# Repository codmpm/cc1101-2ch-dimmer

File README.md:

# CC1101 2ch PWM LED Dimmer

This is a prototype on an 2-channel PWM LED Dimmer which should work with the marvelous AskSin++ library.

Readme will be populated over time...

# License
codm.de, 2019, CC-BY-NC

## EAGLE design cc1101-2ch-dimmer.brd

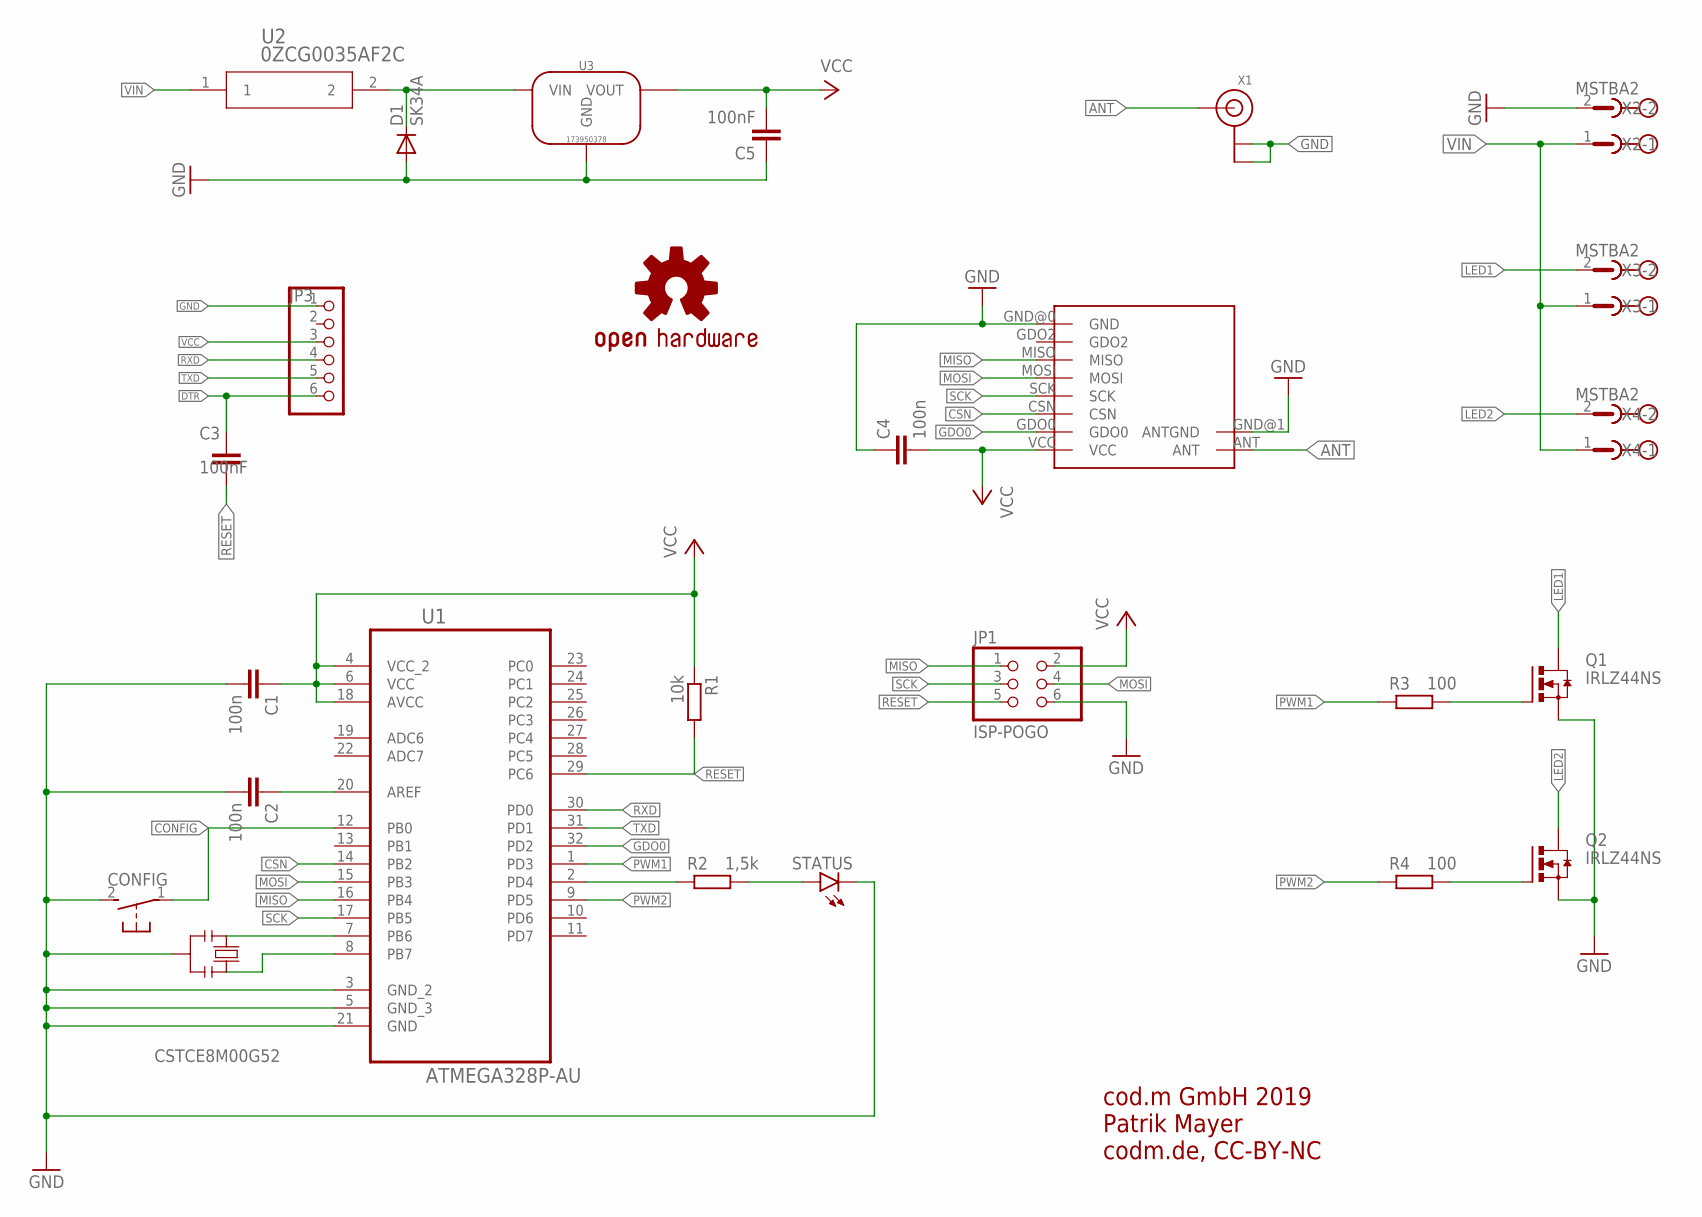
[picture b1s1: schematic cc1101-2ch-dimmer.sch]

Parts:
C1, C2, C4: 100n; C0805
C3, C5: 100nF; C0805
CONFIG: 31-XX; B3F-31XX
D1: SK34A; DO214AC
JP1: ISP-POGO; 2X03
JP3: PINHD-1X6; 1X06
LOGO1: OSHW-LOGOM; OSHW-LOGO-M
Q1, Q2: IRLZ44NS; D2PAK
R1: 10k; R0805
R2: 1,5k; R0805
R3, R4: 100; R0805
STATUS: LEDCHIPLED_0805; CHIPLED_0805
U1: ATMEGA328P-AU; QFP80P900X900X120-32N
U2: 0ZCG0035AF2C; 0ZCG
U3: 173950378; SIP-3
U$1: CC1101-868MS10
X1: ANTENNA_U.FL; U.FL
X2, X3, X4: MSTBA2
Y1: CSTCE8M00G52; RESONATOR

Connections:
ANT: U$1.ANT, X1.3 (SIGNAL)
CONFIG: CONFIG.1, U1.12 (PB0)
CSN: U1.14 (PB2), U$1.CSN
DTR: C3.1, JP3.6
GDO0: U1.32 (PD2), U$1.GDO0
GND: C1.2, C2.2, C4.1, C5.1, CONFIG.2 (S), D1.A, JP1.6, JP3.1, Q1.3 (S), Q2.3 (S), STATUS.C, U1.3 (GND_2), U1.5 (GND_3), U1.21 (GND), U3.P$2 (GND), U$1.GND@0 (GND), U$1.GND@1 (ANTGND), X1.1 (GND), X1.2 (GND), X2.2, Y1.2
LED1: Q1.2 (D), X3.2
LED2: Q2.2 (D), X4.2
MISO: JP1.1, U1.16 (PB4), U$1.MISO
MOSI: JP1.4, U1.15 (PB3), U$1.MOSI
unnamed: R2.1, U1.2 (PD4)
unnamed: R2.2, STATUS.A
unnamed: Q2.1 (G), R4.2
unnamed: U1.7 (PB6), Y1.1
unnamed: Q1.1 (G), R3.2
unnamed: C2.1, U1.20 (AREF)
unnamed: U1.8 (PB7), Y1.3
unnamed: D1.C, U2.2, U3.P$1 (VIN)
PWM1: R3.1, U1.1 (PD3)
PWM2: R4.1, U1.9 (PD5)
RESET: C3.2, JP1.5, R1.2, U1.29 (PC6)
RXD: JP3.4, U1.30 (PD0)
SCK: JP1.3, U1.17 (PB5), U$1.SCK
TXD: JP3.5, U1.31 (PD1)
VCC: C1.1, C4.2, C5.2, JP1.2, JP3.3, R1.1, U1.4 (VCC_2), U1.6 (VCC), U1.18 (AVCC), U3.P$3 (VOUT), U$1.VCC
VIN: U2.1, X2.1, X3.1, X4.1

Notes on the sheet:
cod.m GmbH 2019 Patrik Mayer codm.de, CC-BY-NC

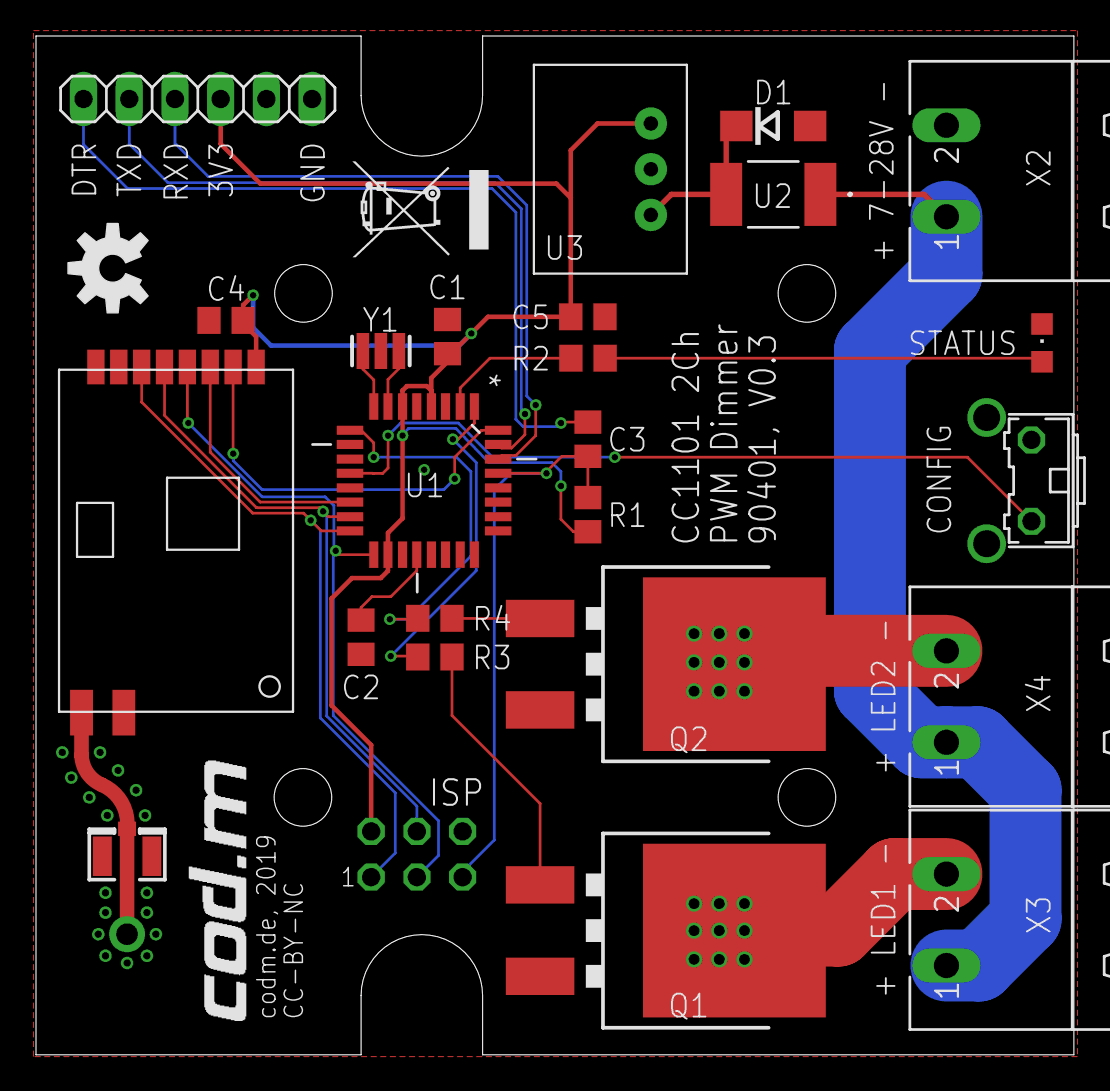
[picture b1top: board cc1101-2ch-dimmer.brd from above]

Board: 2 copper layers, 57.7 x 56.6 mm, 28 parts (0 on the bottom side), 26 nets.

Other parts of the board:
U$2: CODM-LOGO
U$3: WEEE-LOGO-5MM

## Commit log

2019-06-05 finishing touches first prototype
2019-06-05 reworked texts
2019-06-25 added 8mhz resonator, reworked for 0.2
2019-07-05 reworked clearance, used newer aisler dru
2019-08-13 added the chineses cc1101
2019-08-18 minor cleanup
2019-08-18 added info to schematic
2019-08-18 readme, images, info
2019-08-18 optimized images
2019-08-19 fixed wrong symbol for C3

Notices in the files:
parts and their libraries:
SparkFun-Aesthetics: Licensing: Creative Commons ShareAlike 4.0 International - https://creativecommons.org/licenses/by-sa/4.0
